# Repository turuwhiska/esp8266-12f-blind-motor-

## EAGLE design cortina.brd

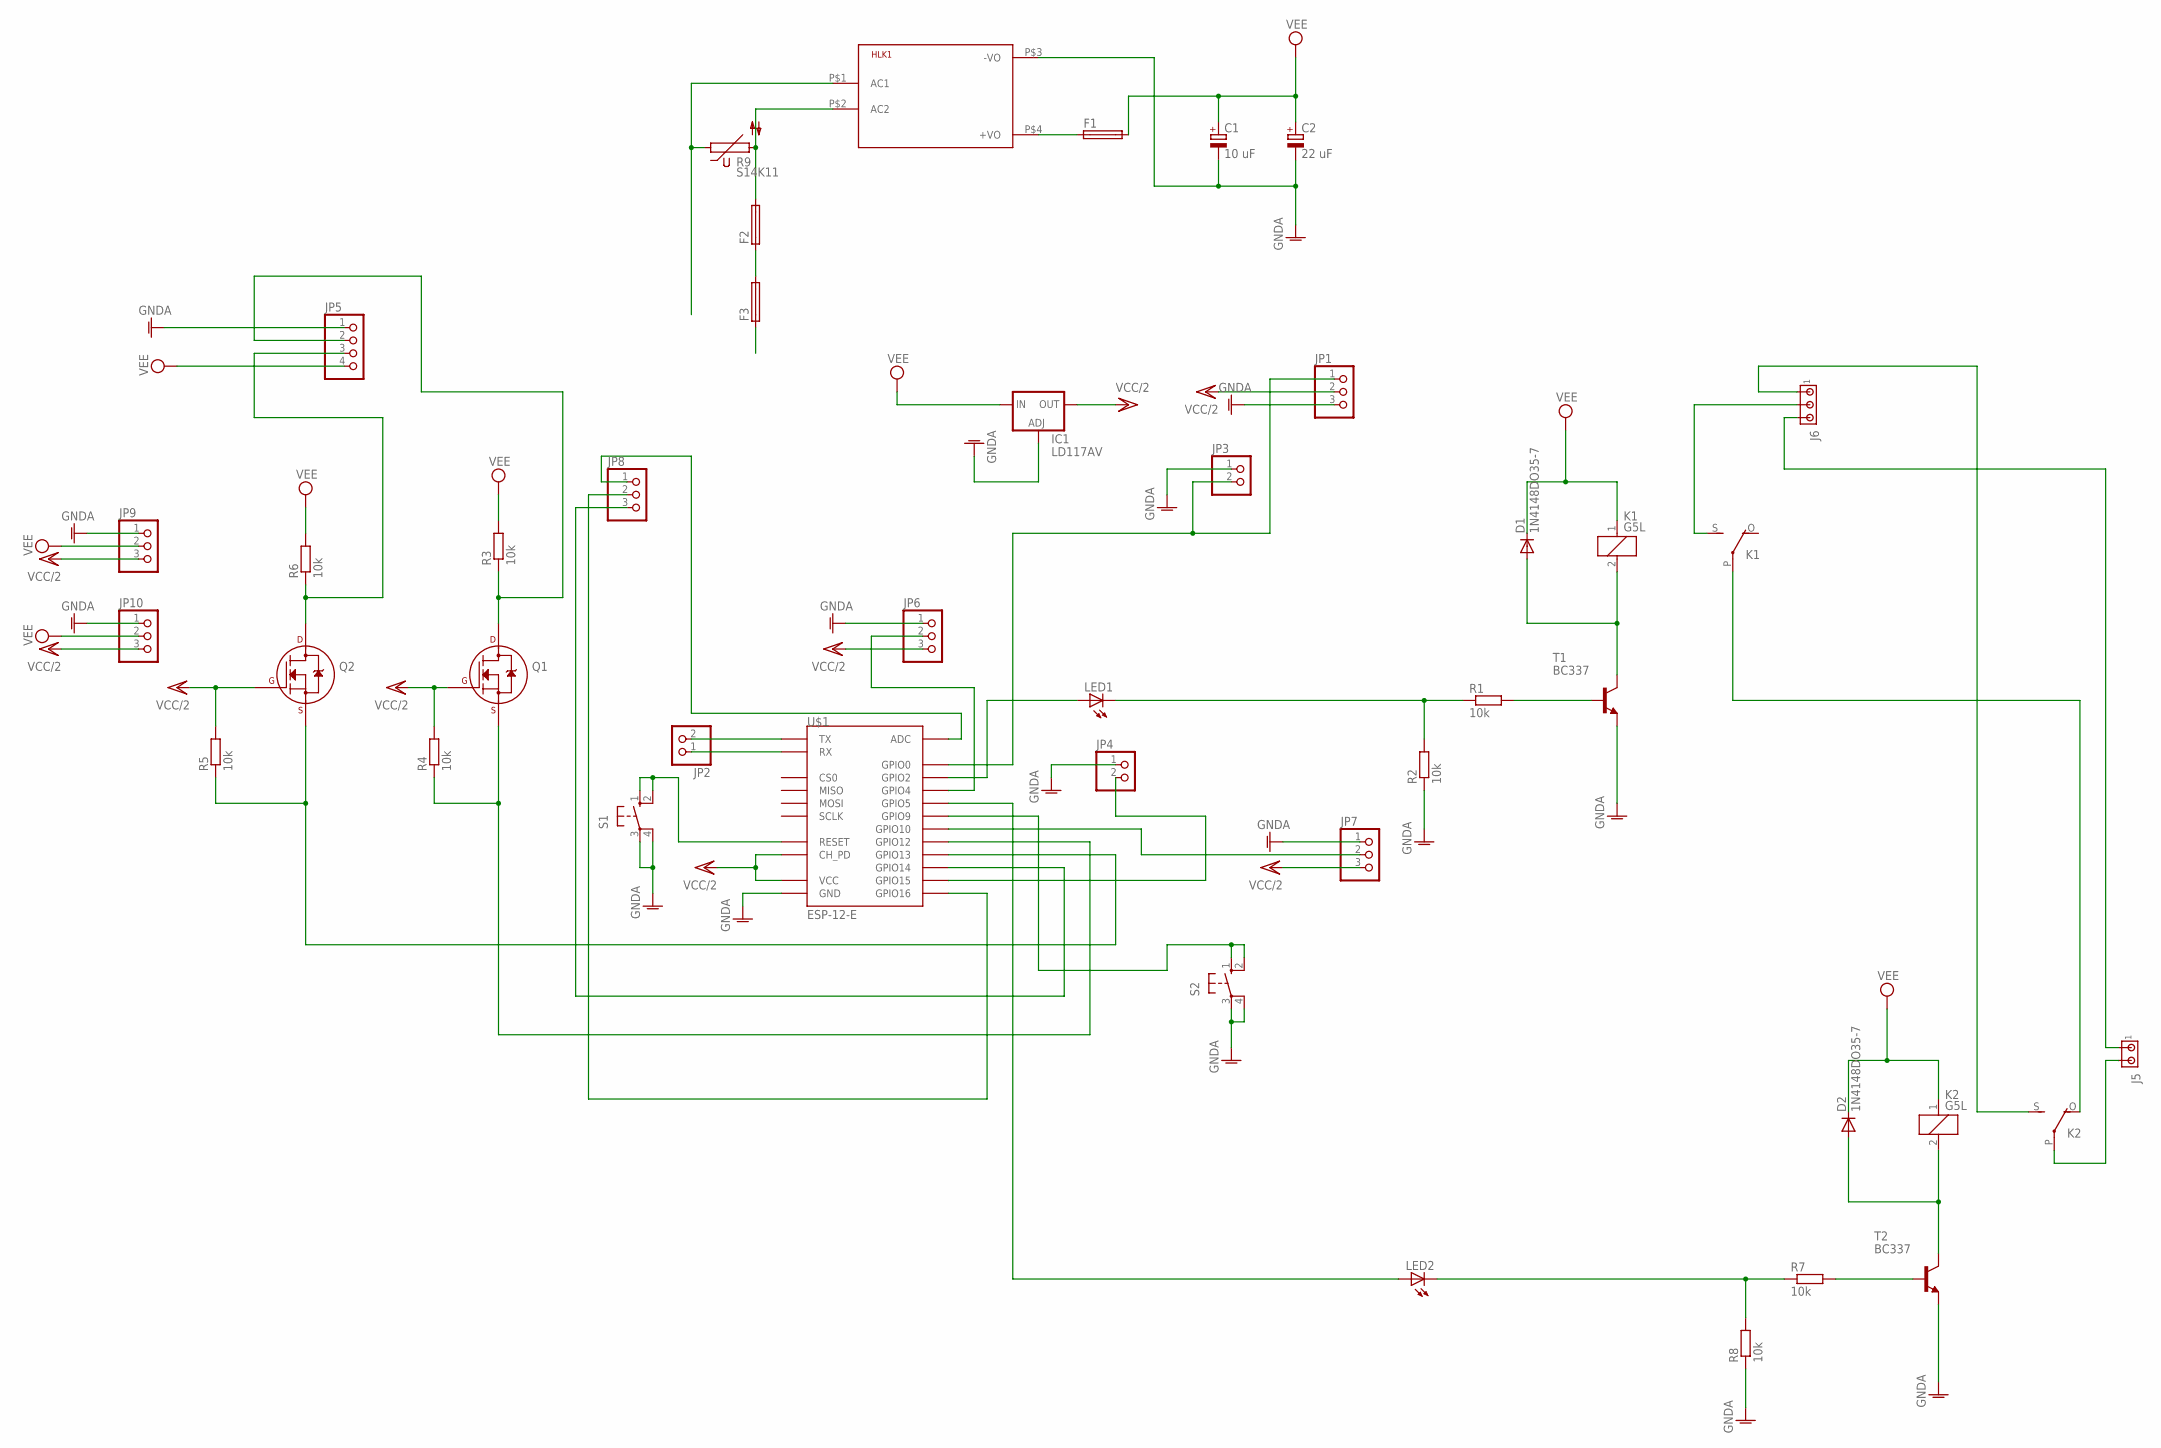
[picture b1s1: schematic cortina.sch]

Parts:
C1: 10 uF; E1,8-4
C2: 22 uF; E1,8-4
D1, D2: 1N4148DO35-7; DO35-7
F1, F2, F3: GSH15
HLK1: HLK-PM013W; HLK-PM01
IC1: LD117AV; TO220L1
J5: MTA02-156; 1X2MTA
J6: MTA03-156; 1X3MTA
JP1, JP6, JP7, JP8, JP9, JP10: PINHD-1X3; 1X03
JP2, JP3, JP4: PINHD-1X2; 1X02
JP5: PINHD-1X4; 1X04
K1, K2: G5L; G5LE
LED1, LED2: LED5MM
Q1, Q2: 2N7002_TO92; TO-92
R1, R2, R3, R4, R5, R6, R7, R8: 10k; 0207/7
R9: S14K11
S1, S2: 10-XX; B3F-10XX
T1, T2: BC337; TO92
U$1: ESP-12-E

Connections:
GNDA: C1.-, C2.-, HLK1.P$3 (-VO), IC1.1 (ADJ), JP1.3, JP3.1, JP4.1, JP5.1, JP6.1, JP7.1, JP9.1, JP10.1, R2.1, R8.1, S1.3, S1.4 (P1), S2.3, S2.4 (P1), T1.1 (E), T2.1 (E), U$1.GND
unnamed: HLK1.P$1 (AC1), J5.1, J6.3, R9.1
unnamed: LED1.A, U$1.GPIO2
unnamed: JP1.1, JP3.2, U$1.GPIO0
unnamed: LED1.K (C), R1.1, R2.2
unnamed: JP2.2, U$1.TX
unnamed: D1.A, K1.2, T1.3 (C)
unnamed: R1.2, T1.2 (B)
unnamed: J6.2, K1.S
unnamed: K1.P, K2.O
unnamed: JP2.1, U$1.RX
unnamed: Q1.1 (S), R4.1, U$1.GPIO12
unnamed: JP5.2, Q1.3 (D), R3.1
unnamed: D2.A, K2.2, T2.3 (C)
unnamed: Q2.1 (S), R5.1, U$1.GPIO13
unnamed: JP5.3, Q2.3 (D), R6.1
unnamed: JP4.2, U$1.GPIO15
unnamed: JP6.2, U$1.GPIO4
unnamed: JP7.2, LED2.A, U$1.GPIO5, U$1.GPIO10
unnamed: JP8.1, U$1.ADC
unnamed: JP8.3, U$1.GPIO14
unnamed: JP8.2, U$1.GPIO16
unnamed: R7.2, T2.2 (B)
unnamed: F1.1, HLK1.P$4 (+VO)
unnamed: J6.1, K2.S
unnamed: F3.1, J5.2, K2.P
unnamed: LED2.K (C), R7.1, R8.2
unnamed: F2.1, F3.2
unnamed: F2.2, HLK1.P$2 (AC2), R9.2
unnamed: S1.1 (S), S1.2 (S1), U$1.RESET
unnamed: S2.1 (S), S2.2 (S1), U$1.GPIO9
VCC/2: IC1.2 (OUT), JP1.2, JP6.3, JP7.3, JP9.3, JP10.3, Q1.2 (G), Q2.2 (G), R4.2, R5.2, U$1.CH_PD, U$1.VCC
VEE: C1.+, C2.+, D1.C, D2.C, F1.2, IC1.3 (IN), JP5.4, JP9.2, JP10.2, K1.1, K2.1, R3.2, R6.2

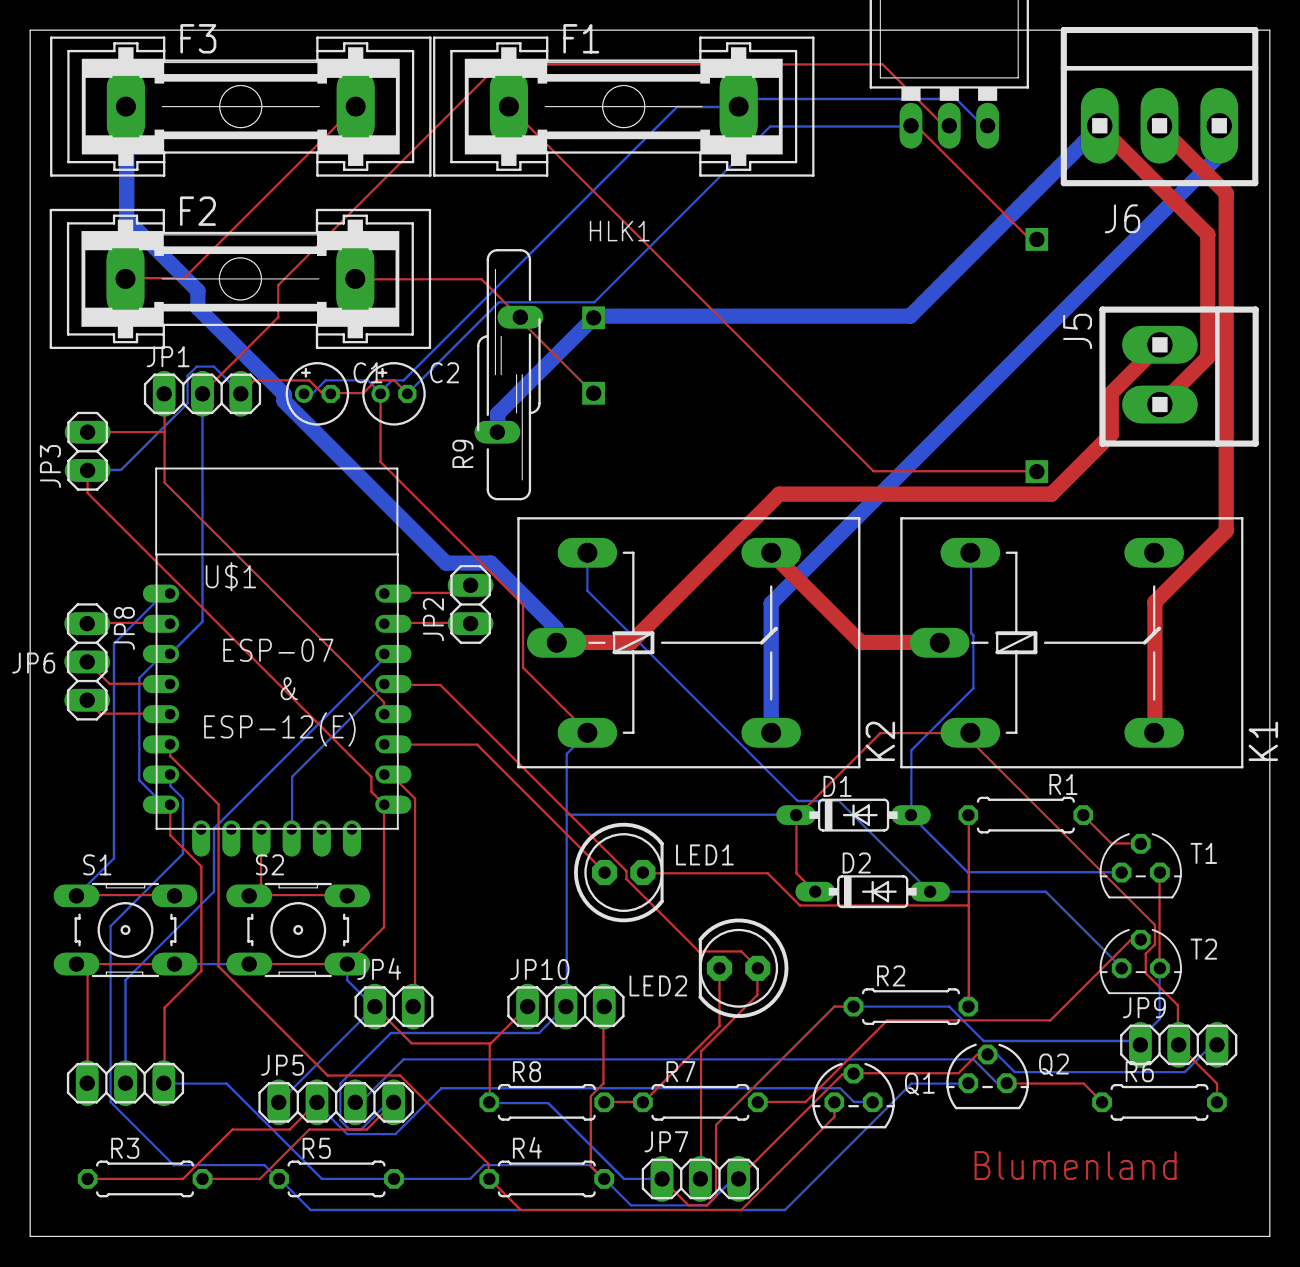
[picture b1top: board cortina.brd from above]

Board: 2 copper layers, 82.2 x 80.0 mm, 41 parts (0 on the bottom side), 33 nets.

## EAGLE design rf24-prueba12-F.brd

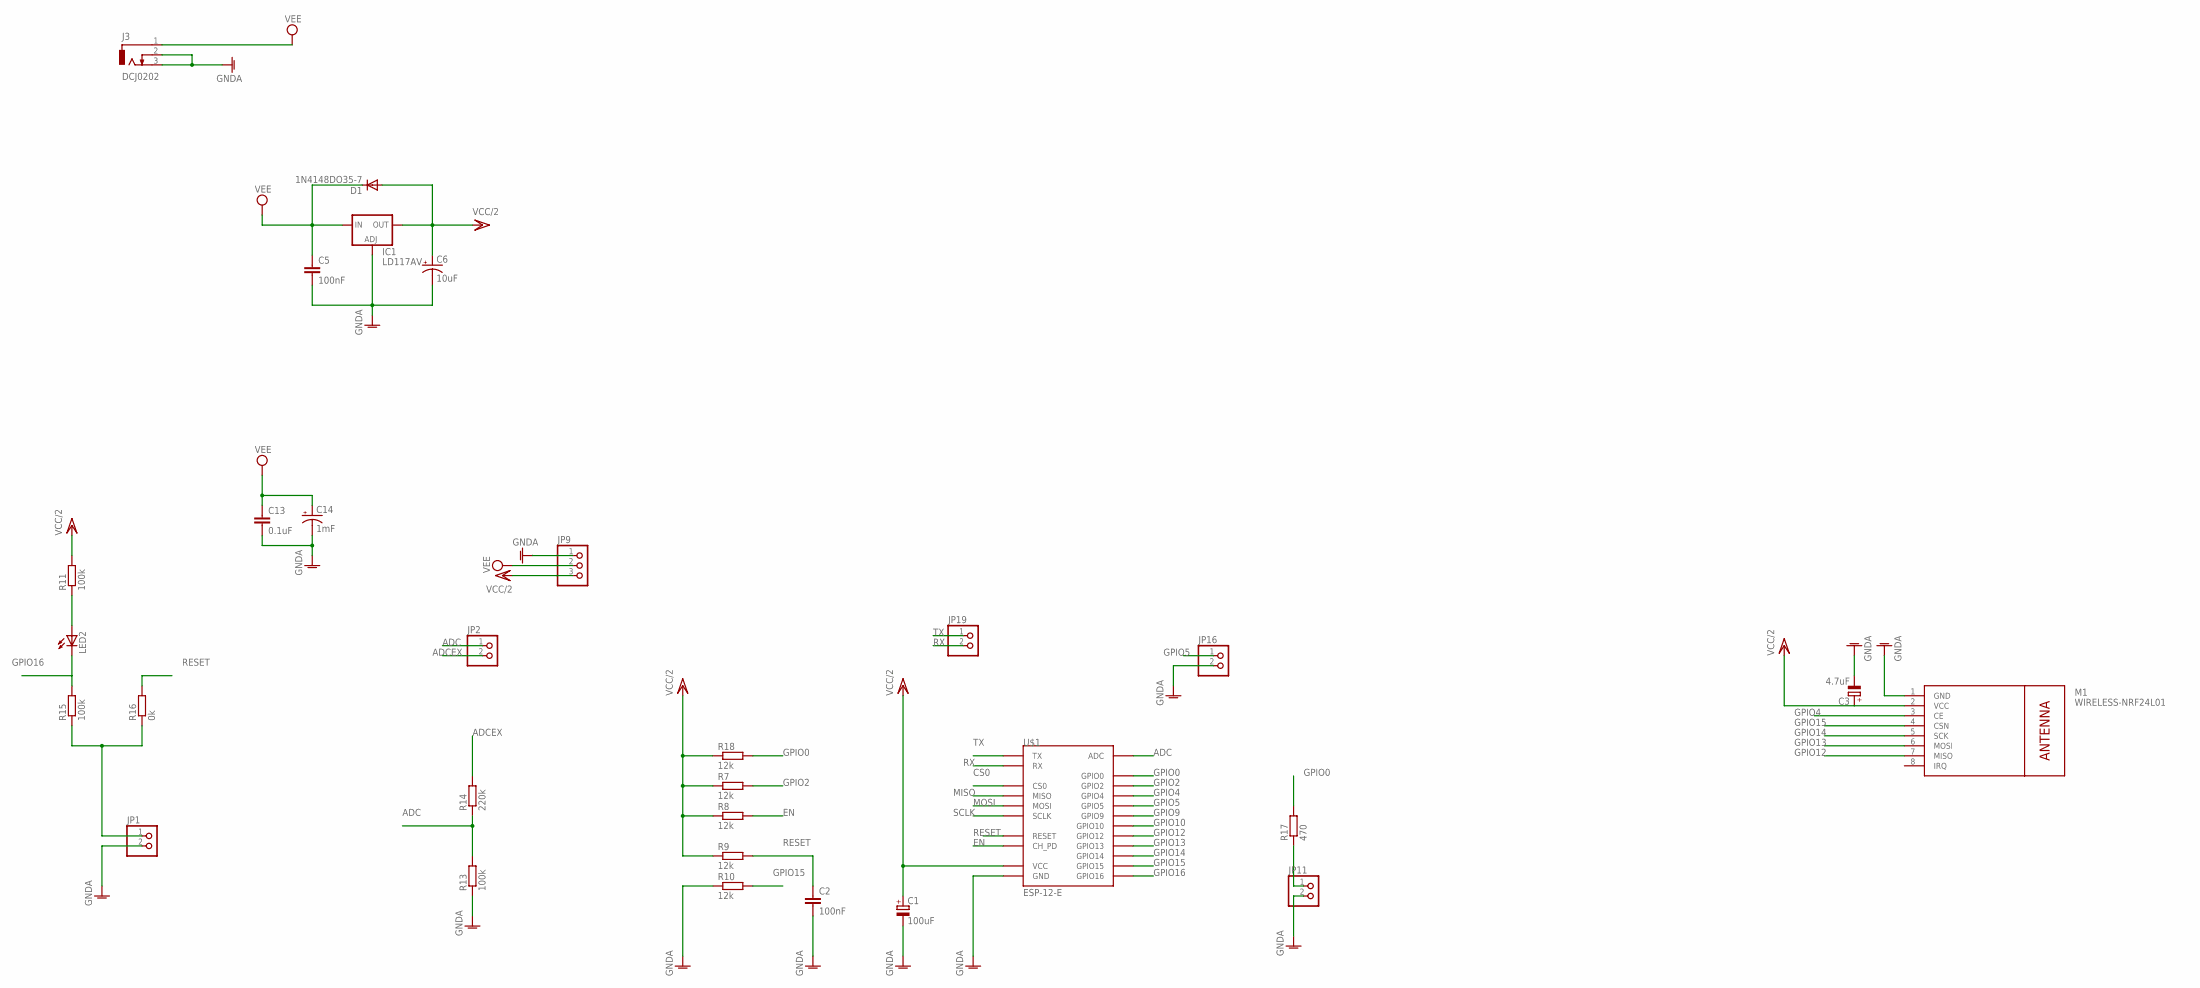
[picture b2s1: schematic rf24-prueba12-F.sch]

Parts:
C1: 100uF; TT5D7
C2: 100nF; C025-024X044
C3: 4.7uF; TT5D7
C5: 100nF; C025-025X050
C6: 10uF; E2,5-6E
C13: 0.1uF; C025-025X050
C14: 1mF; E2,5-6E
D1: 1N4148DO35-7; DO35-7
IC1: LD117AV; TO220L1
J3: DCJ0202
JP1, JP2, JP11, JP16, JP19: PINHD-1X2; 1X02
JP9: PINHD-1X3; 1X03
LED2: LED3MM
M1: WIRELESS-NRF24L01
R7, R8, R9, R10, R18: 12k; 0207/7
R11, R13, R15: 100k; 0207/7
R14: 220k; 0207/7
R16: 0k; 0207/7
R17: 470; 0207/7
U$1: ESP-12-E

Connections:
ADC: JP2.1, R13.2, R14.1, U$1.ADC
ADCEX: JP2.2, R14.2
CS0: U$1.CS0
EN: R8.2, U$1.CH_PD
GNDA: C1.-, C2.2, C3.-, C5.2, C6.-, C13.2, C14.-, IC1.1 (ADJ), J3.2, J3.3, JP1.2, JP9.1, JP11.2, JP16.2, M1.1 (GND), R10.1, R13.1, U$1.GND
GPIO0: R17.2, R18.2, U$1.GPIO0
GPIO2: R7.2, U$1.GPIO2
GPIO4: M1.3 (CE), U$1.GPIO4
GPIO5: JP16.1, U$1.GPIO5
GPIO9: U$1.GPIO9
GPIO10: U$1.GPIO10
GPIO12: M1.7 (MISO), U$1.GPIO12
GPIO13: M1.6 (MOSI), U$1.GPIO13
GPIO14: M1.5 (SCK), U$1.GPIO14
GPIO15: M1.4 (CSN), R10.2, U$1.GPIO15
GPIO16: LED2.K (C), R15.2, U$1.GPIO16
MISO: U$1.MISO
MOSI: U$1.MOSI
unnamed: JP11.1, R17.1
unnamed: LED2.A, R11.1
unnamed: JP1.1, R15.1, R16.1
RESET: C2.1, R9.2, R16.2, U$1.RESET
RX: JP19.2, U$1.RX
SCLK: U$1.SCLK
TX: JP19.1, U$1.TX
VCC/2: C1.+, C3.+, C6.+, D1.A, IC1.2 (OUT), JP9.3, M1.2 (VCC), R7.1, R8.1, R9.1, R11.2, R18.1, U$1.VCC
VEE: C5.1, C13.1, C14.+, D1.C, IC1.3 (IN), J3.1, JP9.2

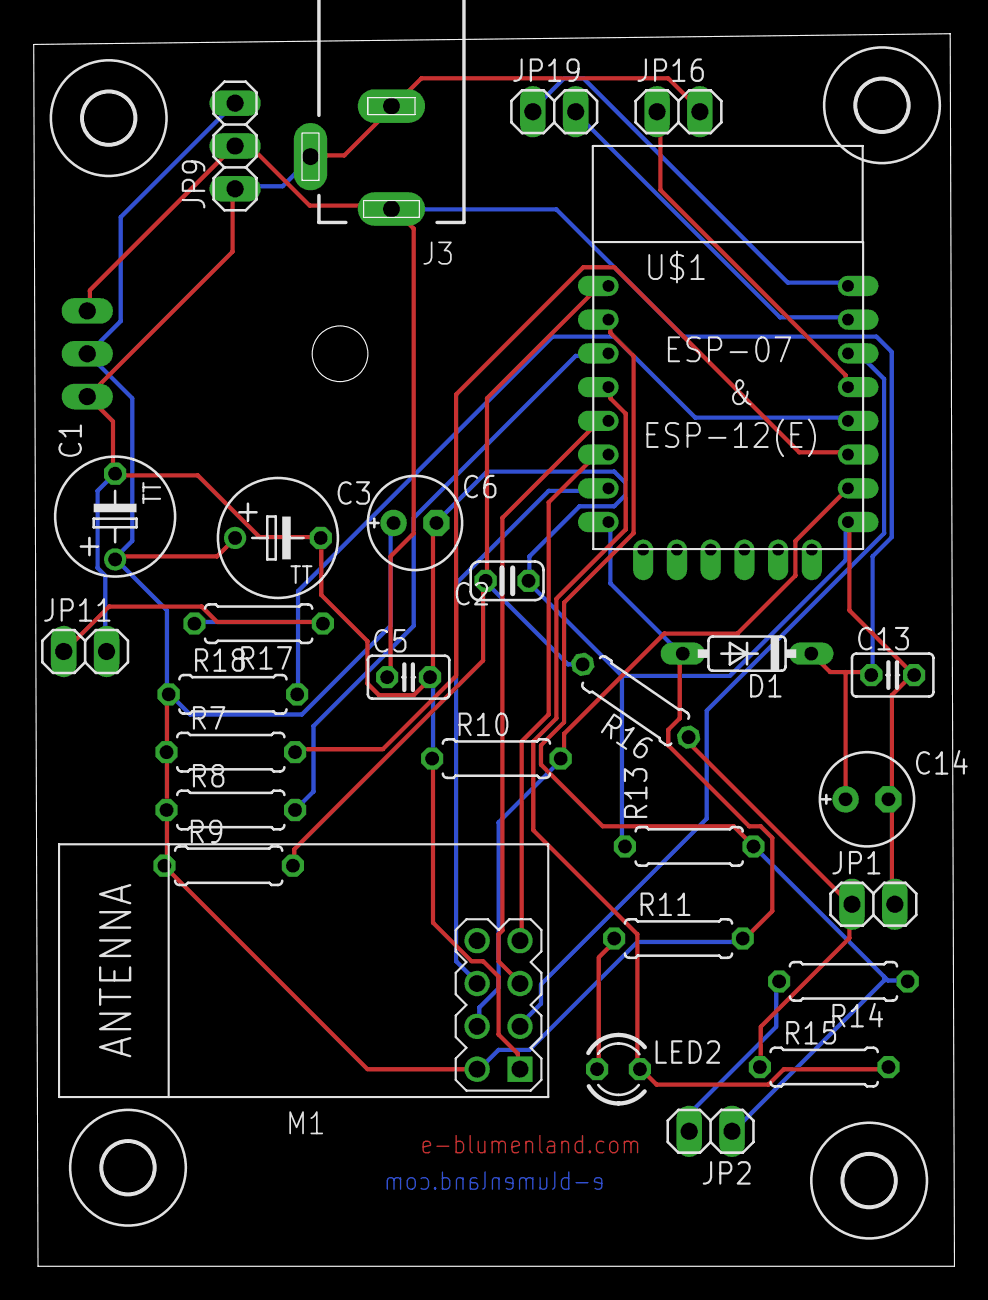
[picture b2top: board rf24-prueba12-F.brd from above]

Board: 2 copper layers, 54.6 x 73.1 mm, 34 parts (1 on the bottom side), 21 nets.

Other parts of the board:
H1, H2, H7, H8: MOUNT-HOLE3.0; 3,0

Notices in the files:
parts and their libraries:
diy-modules: Released under the Creative Commons Attribution 4.0 International License: http://creativecommons.org/licenses/by/4.0
